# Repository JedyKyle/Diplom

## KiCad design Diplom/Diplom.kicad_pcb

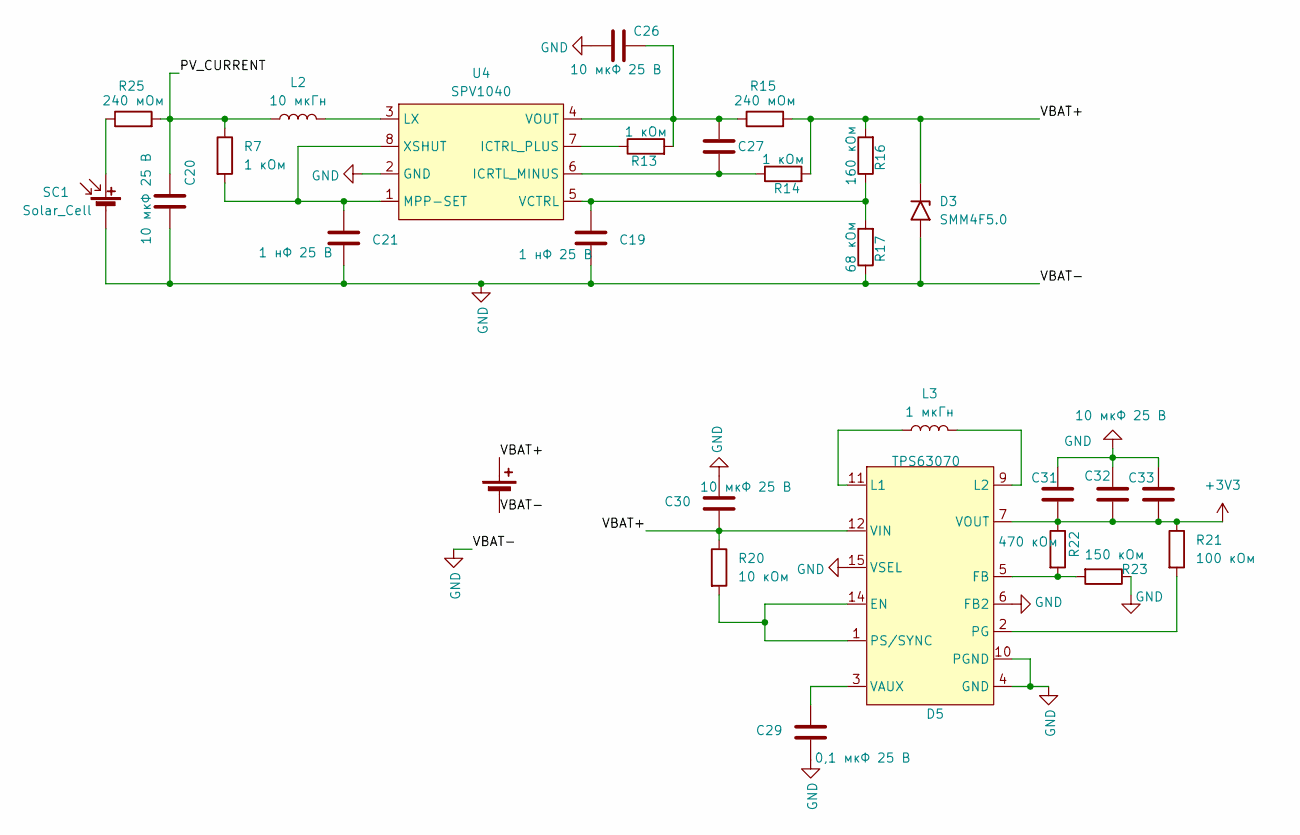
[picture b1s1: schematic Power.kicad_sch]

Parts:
BT1: Battery_Cell; SolderWire-0.75sqmm_1x02_P4.8mm_D1.25mm_OD2.3mm
C19, C21: 1 нФ 25 В; C_0603_1608Metric_Pad1.08x0.95mm_HandSolder
C20, C26, C30, C31, C32, C33: 10 мкФ 25 В; C_0603_1608Metric_Pad1.08x0.95mm_HandSolder
C27: 1 мкФ 25 В; C_0603_1608Metric_Pad1.08x0.95mm_HandSolder
C29: 0,1 мкФ 25 В; C_0603_1608Metric_Pad1.08x0.95mm_HandSolder
D3: SMM4F5.0; D_SMB
D5: TPS63070; VQFN-15_2.5x3_Pitch0.5mm
L2: 10 мкГн; L_Neosid_SMS-ME3015
L3: 1 мкГн; L_Wurth_WE-LQSH-3012
R7, R13, R14: 1 кОм; R_0603_1608Metric_Pad0.98x0.95mm_HandSolder
R15, R25: 240 мОм; R_1206_3216Metric
R16: 160 кОм; R_0603_1608Metric_Pad0.98x0.95mm_HandSolder
R17: 68 кОм; R_0603_1608Metric_Pad0.98x0.95mm_HandSolder
R20: 10 кОм; R_0603_1608Metric_Pad0.98x0.95mm_HandSolder
R21: 100 кОм; R_0603_1608Metric_Pad0.98x0.95mm_HandSolder
R22: 470 кОм; R_0603_1608Metric_Pad0.98x0.95mm_HandSolder
R23: 150 кОм; R_0603_1608Metric_Pad0.98x0.95mm_HandSolder
SC1: Solar_Cell; SolderWire-0.75sqmm_1x02_P4.8mm_D1.25mm_OD2.3mm
U4: SPV1040; TSSOP-8_4.4x3mm_P0.65mm

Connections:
/Power/PV_CURRENT: C20.1, L2.1, R7.1, R25.2; also elsewhere on the board
unnamed: D5.1 (PS/SYNC), D5.14 (EN), R20.2
unnamed: D5.5 (FB), R22.2, R23.2
unnamed: D5.11 (L1), L3.1
unnamed: D5.9 (L2), L3.2
unnamed: D5.2 (PG), R21.2
unnamed: C29.2, D5.3 (VAUX)
unnamed: R25.1, SC1.1 (+)
unnamed: C27.1, R14.1, U4.6 (ICRTL_MINUS)
unnamed: R13.1, U4.7 (ICTRL_PLUS)
unnamed: L2.2, U4.3 (LX)
unnamed: C21.1, R7.2, U4.1 (MPP-SET), U4.8 (XSHUT)
unnamed: C19.1, R16.1, R17.2, U4.5 (VCTRL)
unnamed: C26.2, C27.2, R13.2, R15.1, U4.4 (VOUT)

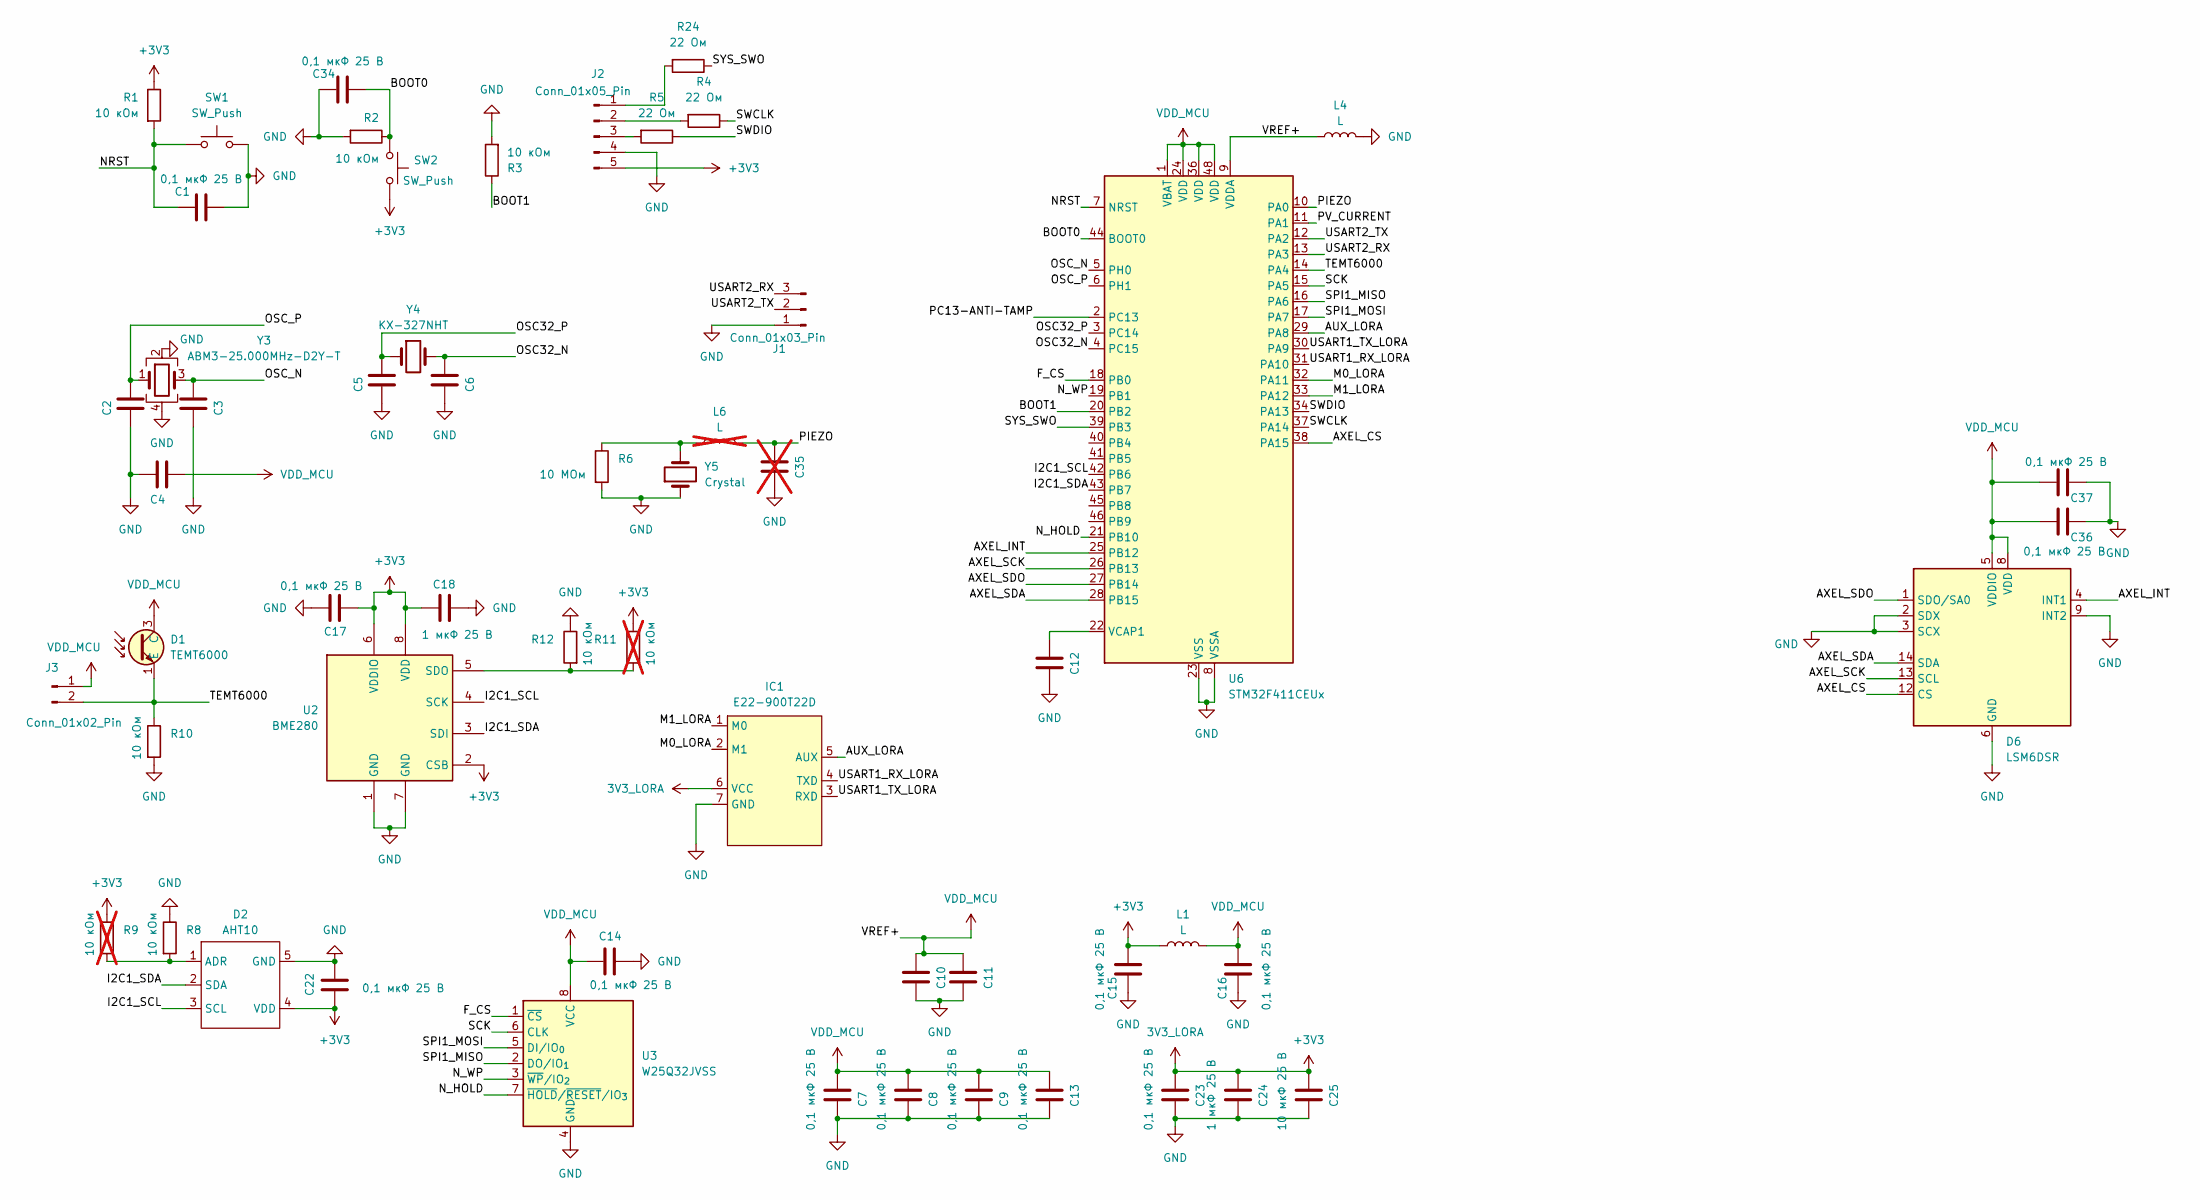
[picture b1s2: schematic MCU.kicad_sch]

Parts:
C1, C4, C7, C8, C9, C11, C13, C14, C15, C16, C17, C22, C23, C34, C36, C37: 0,1 мкФ 25 В; C_0603_1608Metric_Pad1.08x0.95mm_HandSolder
C2, C3: 18 пФ 25 В; C_0603_1608Metric_Pad1.08x0.95mm_HandSolder
C5, C6: 12 пФ 25 В; C_0603_1608Metric_Pad1.08x0.95mm_HandSolder
C10, C18, C24: 1 мкФ 25 В; C_0603_1608Metric_Pad1.08x0.95mm_HandSolder
C12: 4,7 мкФ 25 В; C_0603_1608Metric_Pad1.08x0.95mm_HandSolder
C25: 10 мкФ 25 В; C_0603_1608Metric_Pad1.08x0.95mm_HandSolder
C35: 12 пФ 25 В; C_0603_1608Metric_Pad1.08x0.95mm_HandSolder; not fitted
D1: TEMT6000
D2: AHT10
D6: LSM6DSR; LGA-14_3x2.5mm_P0.5mm_LayoutBorder3x4y
IC1: E22-900T22D; LoRa module
J1: Conn_01x03_Pin; PinHeader_1x03_P2.54mm_Vertical
J2: Conn_01x05_Pin; PinHeader_1x05_P2.54mm_Vertical
J3: Conn_01x02_Pin; PinHeader_1x02_P2.54mm_Vertical
L1: L; L_Neosid_SMS-ME3015
L4: L; L_0805_2012Metric_Pad1.15x1.40mm_HandSolder
L6: L; L_0805_2012Metric_Pad1.15x1.40mm_HandSolder; not fitted
R1, R2, R3, R8, R10, R12: 10 кОм; R_0603_1608Metric_Pad0.98x0.95mm_HandSolder
R4, R5, R24: 22 Ом; R_0603_1608Metric_Pad0.98x0.95mm_HandSolder
R6: 10 МОм; R_0603_1608Metric_Pad0.98x0.95mm_HandSolder
R9, R11: 10 кОм; R_0603_1608Metric_Pad0.98x0.95mm_HandSolder; not fitted
SW1, SW2: SW_Push; FSM8JSMATR
U2: BME280; Bosch_LGA-8_2.5x2.5mm_P0.65mm_ClockwisePinNumbering
U3: W25Q32JVSS; SOIC-8_5.3x5.3mm_P1.27mm
U6: STM32F411CEUx; QFN-48-1EP_7x7mm_P0.5mm_EP5.6x5.6mm
Y3: ABM3-25.000MHz-D2Y-T; Crystal_SMD_3225-4Pin_3.2x2.5mm
Y4: KX-327NHT; Crystal_SMD_EuroQuartz_EQ161-2Pin_3.2x1.5mm_HandSoldering
Y5: Crystal; SolderWire-0.75sqmm_1x02_P4.8mm_D1.25mm_OD2.3mm

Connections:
/MCU/AUX_LORA: IC1.5 (AUX), U6.29 (PA8)
/MCU/AXEL_CS: D6.12 (CS), U6.38 (PA15)
/MCU/AXEL_INT: D6.4 (INT1), U6.25 (PB12)
/MCU/AXEL_SCK: D6.13 (SCL), U6.26 (PB13)
/MCU/AXEL_SDA: D6.14 (SDA), U6.28 (PB15)
/MCU/AXEL_SDO: D6.1 (SDO/SA0), U6.27 (PB14)
/MCU/BOOT0: C34.2, R2.1, SW2.1, U6.44 (BOOT0)
/MCU/BOOT1: R3.1, U6.20 (PB2)
/MCU/F_CS: U3.1 (~CS), U6.18 (PB0)
/MCU/I2C1_SCL: D2.3 (SCL), U2.4 (SCK), U6.42 (PB6)
/MCU/I2C1_SDA: D2.2 (SDA), U2.3 (SDI), U6.43 (PB7)
/MCU/M0_LORA: IC1.2 (M1), U6.32 (PA11)
/MCU/M1_LORA: IC1.1 (M0), U6.33 (PA12)
/MCU/NRST: C1.1, R1.2, SW1.1, U6.7 (NRST)
/MCU/N_HOLD: U3.7 (~HOLD/~RESET/IO_{3}), U6.21 (PB10)
/MCU/N_WP: U3.3 (~WP/IO_{2}), U6.19 (PB1)
/MCU/OSC32_N: C6.1, U6.4 (PC15), Y4.2
/MCU/OSC32_P: C5.1, U6.3 (PC14), Y4.1
/MCU/OSC_N: C3.1, U6.5 (PH0), Y3.3
/MCU/OSC_P: C2.1, U6.6 (PH1), Y3.1
/MCU/PC13-ANTI-TAMP: U6.2 (PC13)
/MCU/PIEZO: C35.1, L6.2, U6.10 (PA0)
/MCU/SCK: U3.6 (CLK), U6.15 (PA5)
/MCU/SPI1_MISO: U3.2 (DO/IO_{1}), U6.16 (PA6)
/MCU/SPI1_MOSI: U3.5 (DI/IO_{0}), U6.17 (PA7)
/MCU/SWCLK: R4.1, U6.37 (PA14)
/MCU/SWDIO: R5.1, U6.34 (PA13)
/MCU/SYS_SWO: R24.1, U6.39 (PB3)
/MCU/TEMT6000: D1.1 (E), J3.2, R10.1, U6.14 (PA4)
/MCU/USART1_RX_LORA: IC1.4 (TXD), U6.31 (PA10)
/MCU/USART1_TX_LORA: IC1.3 (RXD), U6.30 (PA9)
/MCU/USART2_RX: J1.3, U6.13 (PA3)
/MCU/USART2_TX: J1.2, U6.12 (PA2)
/Power/PV_CURRENT: U6.11 (PA1); also elsewhere on the board
unnamed: D2.1 (ADR), R8.2, R9.2
unnamed: J2.1, R24.2
unnamed: J2.2, R4.2
unnamed: J2.3, R5.2
unnamed: L6.1, R6.1, Y5.2
unnamed: R11.2, R12.2, U2.5 (SDO)
unnamed: C12.1, U6.22 (VCAP1)

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
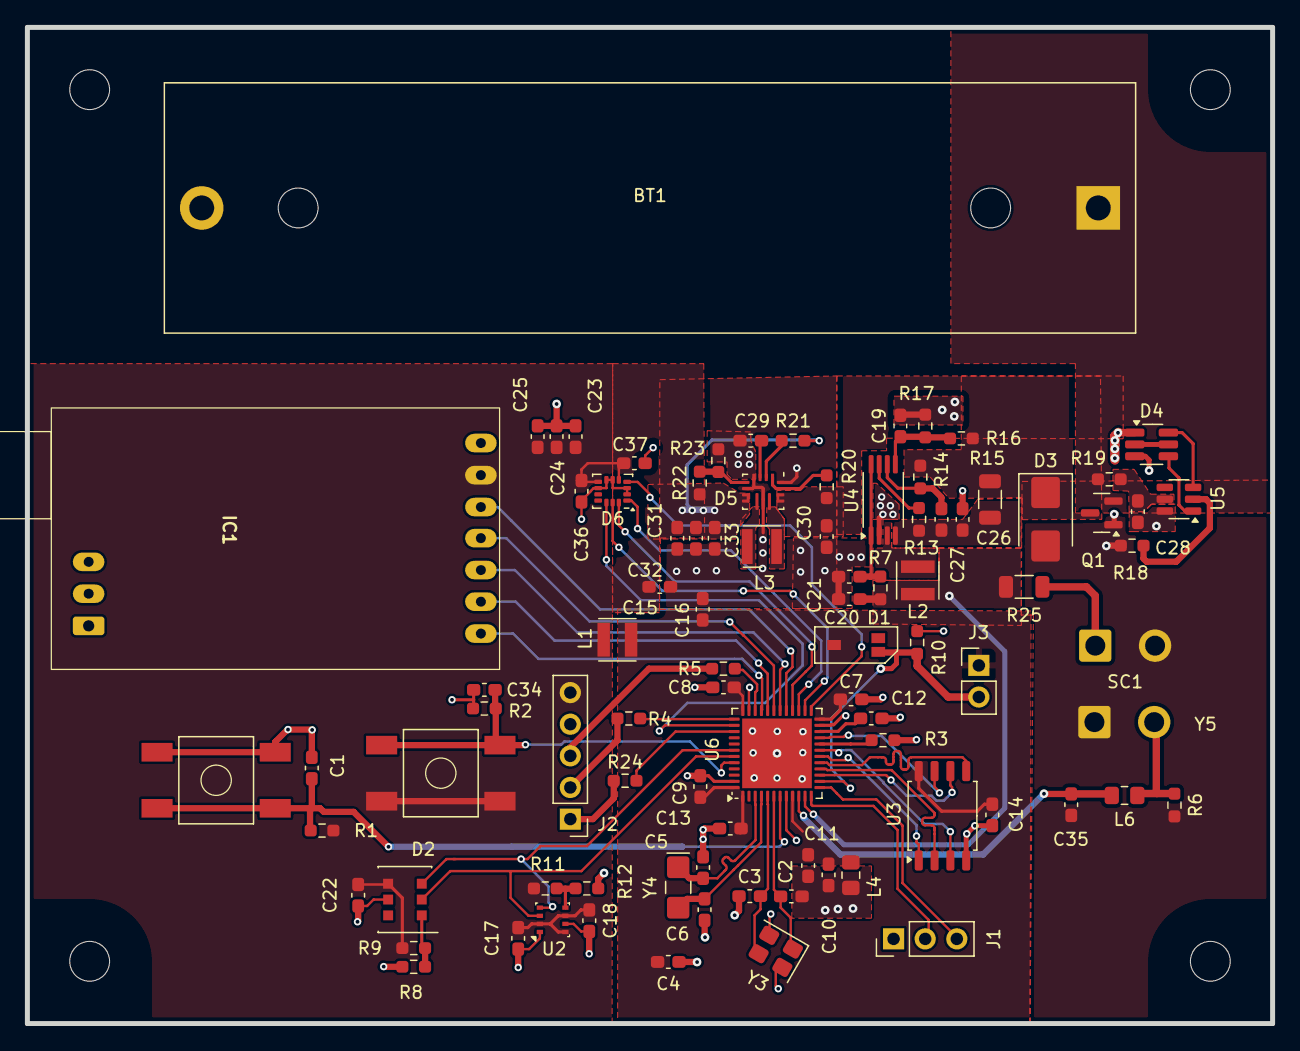
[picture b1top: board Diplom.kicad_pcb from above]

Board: 2 copper layers, 100.0 x 80.0 mm, 90 parts (0 on the bottom side), 64 nets.

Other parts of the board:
C28: 0,1 мкФ 25 В; C_0603_1608Metric_Pad1.08x0.95mm_HandSolder
D4: FS8205A; SOT-23-6_Handsoldering
Q1: SI2301; SOT-23
R18: 1 кОм; R_0603_1608Metric_Pad0.98x0.95mm_HandSolder
R19: 100 Ом; R_0603_1608Metric_Pad0.98x0.95mm_HandSolder
U5: DW01A; SOT-23-6

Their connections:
unnamed: D4.2 (D), D4.5 (D)
unnamed: D4.6 (G), U5.3 (OC)
unnamed: D4.4 (G), U5.1 (OD)
unnamed: R18.1, U5.2 (CS)
unnamed: C28.1, R19.2, U5.5 (VCC)

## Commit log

2025-08-17 START
2025-08-25 version 2.0 fix buttons, roots, tighten dimension
2025-08-25 extra files
2025-08-26 Исправил место под кварц 25МГц, заменил батарею на пакет, перевернул лору. Сырая компоновка без разводки
2025-08-26 corr
2025-09-07 gitignore added
2025-09-07 Add submodule, correction
2025-09-07 Add gitmodule, corrections
2025-09-09 prl deleted
2025-09-24 LSM6 added, fixes
2025-09-25 Corrections on PCB
2025-09-25 corr
    to pay
2025-09-25 Revert "Merge branch 'pr/1' into test"
    This reverts commit 4cbe4dd8ab01a6e23e219b762d34b31485059abc, reversing
    changes made to 124fc186cc7ec1398e475873d0c837433cb920be.
